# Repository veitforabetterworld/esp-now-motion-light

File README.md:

# Funklicht – vernetzter Außen-Bewegungsmelder mit 12-V-Lampe

Wemos D1 mini (ESP8266, Funk per ESP-NOW) + HC-SR501 + MOSFET auf einer **einseitigen THT-Platine (28,5 × 57 mm, v1.2)**,
in einem 3D-gedruckten, **spritzwassergeschützten Gehäuse**. Pro Board: 1 Bewegungsmelder, 1 Lampe, 1 Taster.

## Ordner

| Pfad | Inhalt |
|---|---|
| `hardware/Funklicht.kicad_pro` | KiCad-10-Projekt (Schaltplan + Platine), ERC/DRC fehlerfrei |
| `hardware/jlcpcb/Funklicht_JLCPCB_Gerber.zip` | **Fertig zum Hochladen bei JLCPCB** |
| `hardware/jlcpcb/Stueckliste.csv` | Stückliste |
| `hardware/Funklicht_Schaltplan.pdf`, `Funklicht_3D_*.png`, `Funklicht_Platine.step` | Schaltplan, Ansichten, 3D-Modell |
| `hardware/lib/` | Projekt-Footprints (D1 mini auf Buchsenleisten, Lötaugen PIR, M3-Loch). PIR-Maße nach dem 3D-Modell von [ccadic/HC-SR501](https://github.com/ccadic/HC-SR501) |
| `hardware/scripts/` | Python-Skripte, die Schaltplan und Platine erzeugen (mit KiCads `python.exe` ausführen) |
| `firmware/Funklicht/` | Firmware (ESP-NOW), Einstellungen und Lampentabelle in `config.h` |
| `gehaeuse/Funklicht_Gehaeuse.scad` | Parametrisches Gehäuse (OpenSCAD) |
| `gehaeuse/stl/` | Druckdateien |

## Schaltung

```
12V ─┬──────────────────────────────── Lampe +        Lampe − ── Drain IRLB8721 ── Source ── GND
     ├── HC-SR501 VCC (12 V)                                       Gate ── 220 Ω ── D1 (GPIO5)
     └── 1N4007 ── L7805 ── 5V D1 mini                                     └ 10 kΩ ── GND
```

| D1 mini | Funktion |
|---|---|
| D1 (GPIO5) | MOSFET → Lampe (10 kΩ Pull-down: Lampe bleibt beim Booten aus) |
| D6 (GPIO12) | PIR-Ausgang (3,3 V) |
| D5 (GPIO14) | Taster nach GND (`INPUT_PULLUP`) |
| D4 (GPIO2) | blaue Onboard-LED (Status) |

- **Klemmen** an der Stirnseite: J1 = `+12V | GND` (Einspeisung), J2 = `+ | −` (Lampe).
- **PIR**: 3 Lötaugen `V O G` (VCC, OUT, GND) – Kabel direkt anlöten. Der PIR bekommt 12 V vor der
  Verpolschutzdiode; der HC-SR501 hat selbst eine Schutzdiode, trotzdem **Polarität beim Anschließen prüfen**.
- **Lampenstrom** bis ca. 3 A (Leiterbahnen 1,5 mm, Versorgung 0,8 mm, Signale 0,5 mm; MOSFET ohne Kühlkörper). Keine Freilaufdiode: nur für
  LED-/Halogenlampen gedacht, nicht für Motoren/Relais.

## Stückliste (pro Board)

| Anz. | Teil | Hinweis |
|---|---|---|
| 1 | Wemos D1 mini (ESP8266) | auf **2 × 8-polige Buchsenleisten 8,5 mm** stecken |
| 1 | HC-SR501 | Jumper auf **H** (wiederauslösend), Zeit-Poti auf Minimum |
| 1 | L7805 (TO-220) | stehend |
| 1 | IRLB8721PBF (TO-220) | Logic-Level-MOSFET, stehend. Alternative: IRLB4132PBF (gleiche Pinbelegung und Bauhöhe). Kein Standard-MOSFET wie STP16NF06 oder IRF1404: die schalten mit 3,3 V am Gate nicht sicher durch |
| 1 | 1N4007 | Verpolschutz |
| 1 | Widerstand 220 Ω, 1/4 W | R1 |
| 1 | Widerstand 10 kΩ, 1/4 W | R2 |
| 1 | 1 µF Keramik, RM 2,5 | |
| 1 | 10 µF / 16 V Elko, Ø 5 mm, **max. 6 mm hoch** (z. B. 5 × 5) | sitzt **unter** dem D1 mini |
| 2 | Schraubklemme 2-polig, RM 5,08 | |
| 1 | Taster 6 × 6 × 5 mm, 4 Pins | Höhe 5 mm (Tastenstift ist darauf abgestimmt) |
| 11 | Einschmelzmutter M3 (z. B. M3 × 5,7, Bohrung 4,0 mm) | 4 Bodendeckel, 4 Klemmendeckel, 3 Platine |
| 4 | Senkkopfschraube M3 × 10 (DIN 7991) | Bodendeckel, bündig |
| 4 | Senkkopfschraube M3 × 8 (DIN 7991) | Klemmendeckel, bündig |
| 3 | Zylinderschraube M3 × 6 | Platine |
| 2 | Schneidschraube M2 × 6 (für Kunststoff) | PIR an die Front |
| 2 | Kabelverschraubung M12 × 1,5 | Kabel 3–6,5 mm |
| 2 | Schraube + Dübel, ca. 4 mm | Wandmontage durch die Langlöcher |

## Platine bestellen (JLCPCB)

`hardware/jlcpcb/Funklicht_JLCPCB_Gerber.zip` hochladen. Einstellungen: **2 Lagen** (gleicher Preis wie 1 Lage,
durchkontaktierte Lötaugen lassen sich besser löten – Leiterbahnen liegen trotzdem nur unten), FR-4, 1,6 mm,
HASL. Kein Bestückungsservice nötig.

**Bestückungsdruck nur auf der Unterseite** (Lötseite), die Oberseite bleibt ohne Druck. Jedes Bauteil ist dort
mit Umriss, Symbol und Wert an seiner echten Position eingezeichnet. Die Platine lässt sich allein danach bestücken:
- Widerstände mit Wert (10 kΩ, 220 Ω), Diode 1N4007 mit Ring zur Kathode
- Elko 10 µF mit `+` am eckigen Pad, 1 µF-Kondensator
- L7805 und IRLB8721: Doppellinie = Kühlfahne (Metallseite)
- D1-mini-Buchsenleisten mit Pin-1-Pfeil (RST) und „Antenne hier“
- Taster, PIR-Lötaugen `V O G`, Klemmen `+12V GND` und Lampe `+ −`

Von unten gesehen ist alles spiegelbildlich zur Oberseite. Die Bauteile also von oben einstecken und an der Markierung
auf der Unterseite ausrichten.

**Bestücken** (flach nach hoch): R1, R2, D1, C1, C2 (unter dem D1 mini!), Taster, Buchsenleisten,
Klemmen, L7805, IRLB8721. PIR-Kabel (ca. 10 cm) an `V O G` löten. Danach D1 mini aufstecken.
Unter dem D1 mini nur Bauteile bis 6 mm Höhe. Die Lötaugen `V O G` liegen in der Aussparung des D1 mini.
**Zwei Befestigungsschrauben liegen unter dem D1 mini** – Platine erst festschrauben, dann den D1 mini aufstecken.

Befestigungslöcher (Platinenkoordinaten, Ursprung oben links): H1 (4,07 / 41,39), H2 (24,0 / 32,0), H3 (7,88 / 11,54).
Der Schaltplan (`Funklicht_Schaltplan.pdf`) ist durchgehend verdrahtet: Versorgung links, D1 mini in der Mitte,
Lampenschaltung rechts, +12V-Schiene oben, GND-Schiene unten.

## Gehäuse (v2.0)

Außen ca. 42 × 81,5 × 43 mm (ohne Wandlaschen). **Öffnung nach hinten zur Wand:**

- **Gehäuse** (Haube): Seitenwände und Front aus einem Stück. In der Front sitzen das PIR-Fenster und der Taster.
  Hinten ist das Gehäuse über den vollen Innenquerschnitt (34 × 73,5 mm) offen. Die Platine passt in Einbaulage gerade
  hindurch (geprüft, auch mit L7805/MOSFET).
- **Bodendeckel** (Wandseite): trägt die Platine auf drei Domen (Ø 6,5 mm, berühren keine Lötstelle) und die beiden
  Wandlaschen. Die Laschen haben gerundete Ecken und je ein Langloch (Ø 4,8 mm, 3 mm Verschiebeweg), um 45° gedreht und
  oben/unten spiegelbildlich (`/` und `\`). Zusammen gleichen die beiden Langlöcher ungenau gebohrte Wandlöcher in jeder Richtung aus.
  Der Bodendeckel wird mit 4 M3-Senkkopfschrauben von hinten bündig an das Gehäuse geschraubt. Die Schrauben greifen in
  Einschmelzmuttern in den vier Eckblöcken am hinteren Rand. Die Eckblöcke liegen außerhalb des Platinenumrisses.
- **Dichtung**: TPU-Schnur in einer Nut im hinteren Gehäuserand, innerhalb der Schrauben, rundum geschlossen.
  Die Dichtfläche liegt an der geschützten Wandseite, nicht mehr an der Front. Ein Zentrierkragen am Bodendeckel führt
  ihn ins Gehäuse.
- **PIR** (HC-SR501, Platine 32 × 24 mm): sitzt mittig auf der Front hinter dem Klemmendeckel. Er wird mit seinen
  **2 Befestigungslöchern** (Ø 2 mm, Abstand 28 mm, am Bauteil gemessen) von innen an zwei kurze Dome in der Front
  geschraubt (M2 × 6, Kunststoff-Schneidschraube / Blechschraube 2,2 mm). Die Löcher in den Domen (Ø 1,7 mm) sind
  Sacklöcher und von außen nicht sichtbar. Die Linsendichtung liegt zwischen Linsenplatte und Front.
- **Taster** bei geschlossenem Gehäuse: nur zwei Teile, die Front mit Führungsrohr und ein Tastenstift.
  - Das Loch in der Front ist als **Rohr** (außen Ø 7,6 mm, Bohrung Ø 4,4 mm) bis 1 mm über den Stiftkopf nach innen
    verlängert, rund 21 mm lange Führung.
  - Der **Tastenstift** (Ø 4 mm) hat unten einen Kopf (Ø 6,5 mm), der auf dem Taster aufliegt. Er steht in Ruhe 1 mm aus
    der Front; der Ring auf der Front markiert die Stelle. Der Kopf verhindert, dass der Stift nach außen herausfällt.
  - Die Stiftdurchführung ist **nicht gedichtet** (0,2 mm Spiel rundum). Bei senkrechter Front und waagrechtem Rohr
    kommt kaum Wasser hinein, ganz dicht wie die Deckel ist sie aber nicht.
- **Kabelverschraubungen** (2 × M12 × 1,5) in der unteren Stirnseite, 16 mm über der Dichtfläche und damit nahe an den
  Klemmeneingängen. Zwischen den Kontermuttern innen und den Klemmen bleiben knapp 4 mm, kein Leerraum mehr. Die
  Kontermuttern (SW 15) mit einer Schlüsselfläche zur Seitenwand drehen; so sind sie frei (geprüft, `kollision_kontermutter`).
- **Klemmendeckel** vorne über den Schraubklemmen: kleiner Schraubdeckel mit 4 M3-Senkkopfschrauben (bündig) und
  eigener TPU-Dichtung. Ein **Quersteg** direkt hinter den Klemmen trennt den Klemmenraum vorne ab und trägt die Dichtung.
  Bei abgenommenem Deckel kommt ein Schraubendreher (Ø 3 mm) senkrecht an alle vier Klemmenschrauben (geprüft).
  Kabel lassen sich so anschließen, ohne das Gehäuse von der Wand zu nehmen. Weil auch dieser Deckel gedichtet ist,
  ist der ganze Innenraum dicht.

Kollisionsprüfungen in der SCAD-Datei (`part` = `kollision`, `kollision_taster`, `kollision_bodendeckel`,
`kollision_klemmdeckel`, `kollision_schraubendreher`, `kollision_kontermutter`, `kollision_einbau`) liefern nur Flächenkontakte bzw. ein leeres
Objekt. `kollision_einbau` prüft, dass die bestückte Platine von hinten bis in ihre Endlage geschoben werden kann.

| Teil (`gehaeuse/stl/`) | Material | Druck |
|---|---|---|
| `gehaeuse.stl` | PETG | Front aufs Bett (schon gedreht), ohne Stützen (Eckblöcke mit 45°-Fase) |
| `bodendeckel.stl` | PETG | Wandseite aufs Bett |
| `klemmdeckel.stl` | PETG | Außenseite aufs Bett (schon gedreht) |
| `tastenstift.stl` | PETG | Kopf aufs Bett |
| `regenschutz.stl` (optional) | PETG | flach, über die Linse kleben |
| `dichtung.stl` | TPU 95A | flach, 100 % Infill (Bodendeckel) |
| `klemmdichtung.stl` | TPU 95A | flach, 100 % Infill (Klemmendeckel, gleiche Schnur 1,8 mm) |
| `linsendichtung.stl` | TPU 95A | flach |

**Montage**:
1. Einschmelzmuttern M3 mit dem Lötkolben setzen: 4 im hinteren Gehäuserand, 4 für den Klemmendeckel,
   3 in den Platinendomen des Bodendeckels.
2. Von hinten ins Gehäuse: PIR mit Linsendichtung auf die Dome schrauben. Gehäuse mit der Front nach unten legen und
   den Tastenstift (Spitze voran) ins Rohr stecken.
3. Platine auf den Bodendeckel schrauben, dann den D1 mini aufstecken.
4. Dichtung in die hintere Nut legen, Bodendeckel einsetzen und mit 4 M3 × 10 Senkkopfschrauben von hinten verschrauben.
5. Das Gehäuse **mit den Kabelverschraubungen nach unten** über die Laschen des Bodendeckels an die Wand schrauben.
6. Kabel durch die Verschraubungen führen und durch die vordere Öffnung anklemmen. Klemmdichtung in die Nut legen und
   den Klemmendeckel mit 4 M3 × 8 Senkkopfschrauben aufschrauben.

## Firmware (ESP-NOW)

`firmware/Funklicht/Funklicht.ino` ist eine Firmware für alle Lampen. Board: **LOLIN(WEMOS) D1 R2 & mini**.
Benötigte Bibliothek: **QuickEspNow 0.8.1** (German Martín, MIT), über den Bibliotheksverwalter der Arduino-IDE installieren.

**Schlüssel anlegen:** Die Firmware erwartet eine Arduino-Bibliothek `Secrets` mit dem gemeinsamen Schlüssel.
Sie ist absichtlich nicht im Repository. Anlegen unter `<Sketchbook>/libraries/Secrets/`:

```
libraries/Secrets/library.properties   name=Secrets
                                        version=1.0.0
libraries/Secrets/src/Secrets.h        #pragma once
                                        #define FUNKLICHT_KEY "eigener-langer-zufaelliger-schluessel"
```

Alle Lampen einer Anlage brauchen denselben Schlüssel.

**Funk mit Empfangsbestätigung**:
- Nachrichten gehen gezielt (Unicast) an die gekoppelten Lampen.
- Der Empfänger bestätigt jede Nachricht, und QuickEspNow wartet im synchronen Modus auf diese Bestätigung.
- Fehlt sie, sendet die Firmware bis zu 4-mal erneut, ähnlich wie TCP. Danach meldet sie im seriellen Monitor `Keine Bestaetigung von …`.
- Gesendet werden nur Zustandswechsel, keine Wiederholungen: je Lampe und Durchgang eine Meldung „Bewegung beginnt“ und eine Meldung „Ruhe“ bzw. „Person weiter“ an jeden Partner.
  Nur bei mehr als 2 Minuten ununterbrochener Bewegung wird die Meldung einmal aufgefrischt.
  Fällt eine Lampe aus, bevor sie „Ruhe“ melden kann, gehen ihre Nachbarn nach spätestens 5 Minuten aus.
- Alle 5 Minuten prüft jede Lampe, ob ihre Partner noch antworten.
- Protokollversion 3: Alle Lampen müssen dieselbe Firmware haben.

**Pairing (Lampen koppeln)**, dynamisch über die feste MAC-Adresse, ohne Neu-Kompilieren:

1. An Lampe A den Taster **1 s halten**. As Lampe blinkt schnell, und A sucht 30 s lang einen Partner.
   Alle Lampen, die schon mit A gekoppelt sind, **blinken langsam** mit. So sieht man sofort, welche gekoppelt sind.
2. An einer **nicht blinkenden** Lampe B den Taster 1 s halten: A und B finden sich automatisch und speichern sich
   gegenseitig im Flash. Zur Bestätigung leuchten beide Lampen 1,5 s lang, danach ist der Pairing-Modus beendet.
3. An einer **langsam blinkenden** Lampe den Taster 1 s halten: Die Kopplung zu A wird auf beiden Seiten gelöst.
   Beide leuchten 1,5 s zur Bestätigung. A bleibt im Pairing-Modus (wieder 30 s), so lassen sich mehrere Lampen nacheinander entkoppeln.

Die blaue LED auf dem D1 mini zeigt dasselbe Muster wie die Lampe.

Jede Lampe kann bis zu 8 Partner haben. Gekoppelt werden **benachbarte** Lampen, also die, die bei Bewegung mit vorleuchten sollen (z. B. Garage links ↔ Garage Mitte ↔ Garage rechts ↔ Haustür).
Koppeln können sich nur Lampen mit demselben Schlüssel
(`FUNKLICHT_KEY` in `libraries/Secrets/src/Secrets.h`, alle Nachrichten sind mit HMAC-SHA256 signiert).

**Verhalten**:

| Ereignis | Reaktion |
|---|---|
| Bewegung am eigenen PIR | Licht an bis 60 s nach der letzten Bewegung. Die gekoppelten Lampen bekommen **eine** Meldung „Bewegung beginnt“ |
| 30 s keine Bewegung mehr | Meldung „Ruhe“ an die gekoppelten Lampen, diese gehen aus |
| Gekoppelte Lampe meldet Bewegung | Licht leuchtet vor, bis diese Lampe „Ruhe“ oder „Person weiter“ meldet |
| Person geht von Lampe A zu Lampe B weiter | A meldet „Person weiter“. A und die von A vorgeleuchteten Lampen gehen nach 8 s aus, das Licht folgt der Person. Sieht As PIR die Person noch, erst wenn er abfällt. Weitere Meldungen von B lassen A nicht wieder vorleuchten |
| Taster kurz | wie Bewegung am PIR: Licht an, gekoppelte Lampen werden informiert |
| Taster lang (ab 1 s) | Pairing-Modus. Blinkt die Lampe gerade langsam (Partner ist im Pairing-Modus): Kopplung lösen |

Weitere Eigenschaften:
- Die Lampe wird weich per PWM ein- und ausgeblendet. Flackert ein LED-Treiber, `DIMMEN = false` setzen.
- Der PIR wird 60 s lang ignoriert, solange er anläuft; in dieser Zeit blinkt die LED langsam.
- Ein PIR-Signal zählt erst, wenn es 100 ms ansteht.
- Die Sendeleistung ist auf 17 dBm reduziert.

Alle Einstellungen stehen in `config.h`. Den seriellen Monitor mit 115200 Baud öffnen: Dort zeigt jede Lampe ihre MAC, ihre Partner und alle Funkereignisse.
## Hinweise / offen

- **Fehlauslöser durch Funk:** Der PIR sitzt nah am ESP8266. Gegenmaßnahmen:
  - Der PIR wird mit 12 V versorgt und ist so von der 5-V-Versorgung des ESP getrennt.
  - Der PIR sitzt über dem USB-Ende des Moduls, von der Antenne weg.
  - In der Firmware lässt sich die Sendeleistung reduzieren (`WiFi.setOutputPower()`), eine Entprellung von ca. 100 ms einbauen und die ersten 60 s nach dem Start ignorieren.
- **Ungeprüfte Annahmen:**
  - Die PIR-Maße stammen aus dem 3D-Modell und sind nicht nachgemessen.
  - Die Bauteilhöhen sind Schätzwerte.
  - Vor dem ersten Druck einmal PIR-Platine, Linsendurchmesser (Lochabstand 28 mm ist gemessen) nachmessen. Die Werte stehen oben in der `.scad` (`pir_hole_dx`).
- **Firmware:** kompiliert fehlerfrei, ist aber noch nicht auf echter Hardware mit mehreren Lampen getestet.

## Lizenz

[PolyForm Noncommercial 1.0.0](LICENSE): frei nutzbar, veränderbar und weitergebbar, aber nur nicht kommerziell. Keine Gewährleistung, keine Haftung.

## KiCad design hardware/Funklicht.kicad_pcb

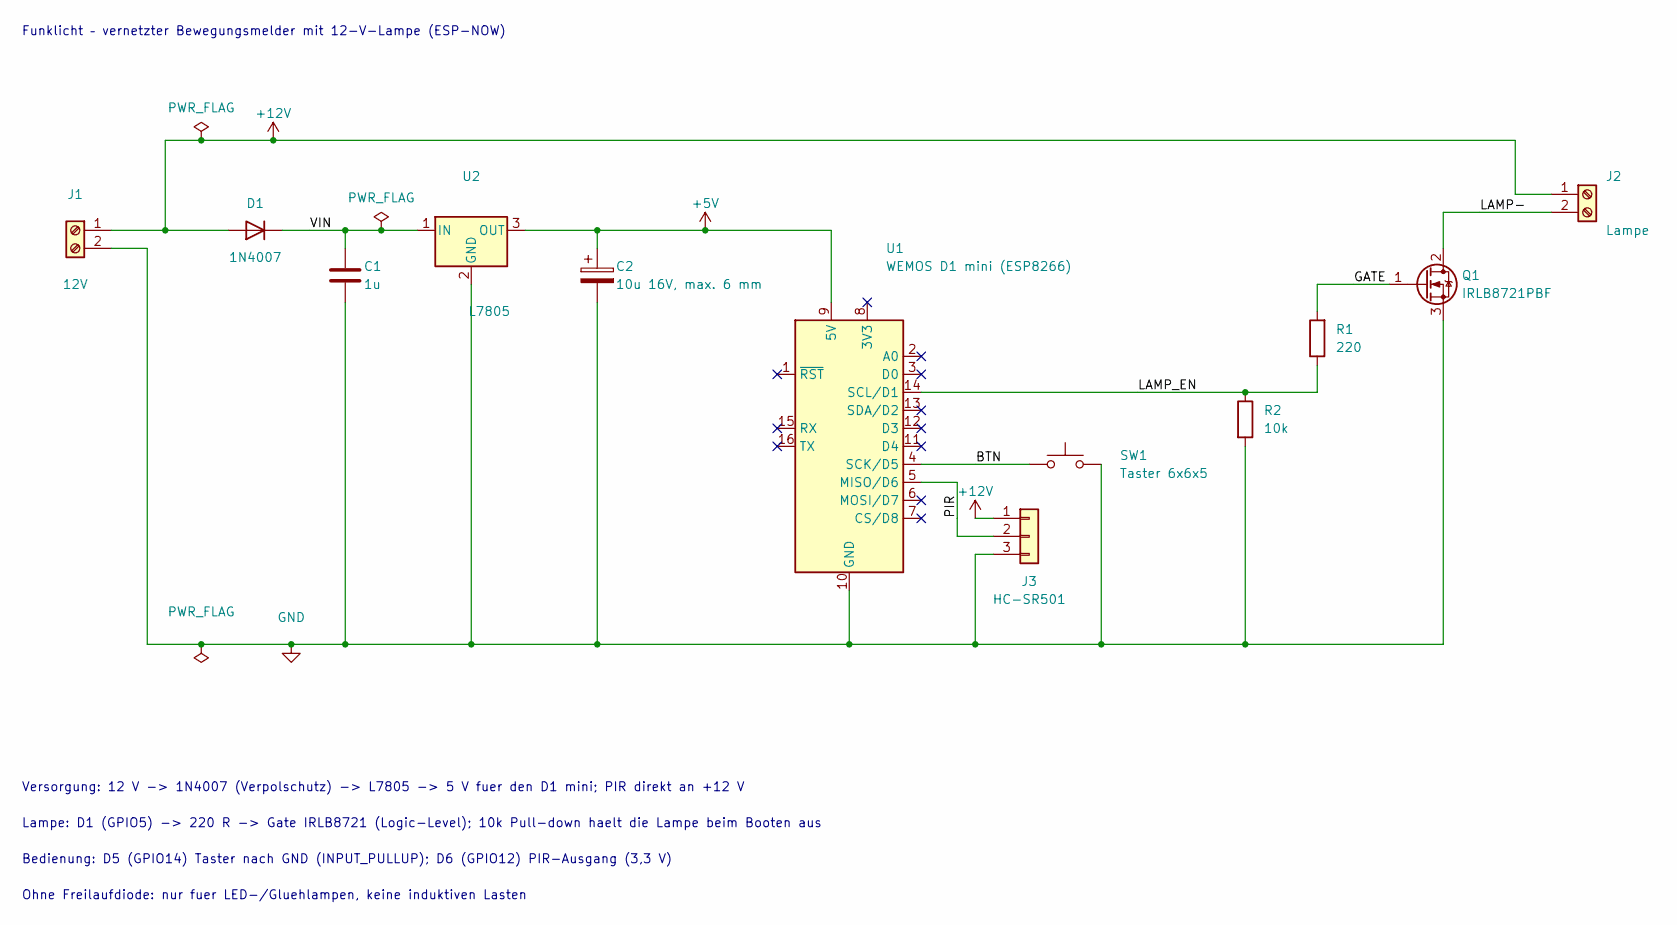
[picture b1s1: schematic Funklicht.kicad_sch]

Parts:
C1: 1u; C_Disc_D3.0mm_W1.6mm_P2.50mm
C2: 10u 16V, max. 6 mm; CP_Radial_D5.0mm_P2.50mm
D1: 1N4007; D_DO-41_SOD81_P10.16mm_Horizontal
J1: 12V; TerminalBlock_Phoenix_MKDS-1,5-2-5.08_1x02_P5.08mm_Horizont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
J2: Lampe; TerminalBlock_Phoenix_MKDS-1,5-2-5.08_1x02_P5.08mm_Horizont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
J3: HC-SR501; Loetaugen_1x03_P2.54mm
Q1: IRLB8721PBF; TO-220-3_Vertical
R1: 220; R_Axial_DIN0207_L6.3mm_D2.5mm_P10.16mm_Horizontal
R2: 10k; R_Axial_DIN0207_L6.3mm_D2.5mm_P10.16mm_Horizontal
SW1: Taster 6x6x5; SW_PUSH_6mm
U1: WEMOS D1 mini (ESP8266); WEMOS_D1_mini_Sockel
U2: L7805; TO-220-3_Vertical

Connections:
+5V: C2.1, U1.9 (5V), U2.3 (OUT)
+12V: D1.2 (A), J1.1, J2.1, J3.1
/BTN: SW1.1, U1.4 (SCK/D5)
/GATE: Q1.1 (G), R1.2
/LAMP-: J2.2, Q1.2 (D)
/LAMP_EN: R1.1, R2.1, U1.14 (SCL/D1)
/PIR: J3.2, U1.5 (MISO/D6)
/VIN: C1.1, D1.1 (K), U2.1 (IN)
GND: C1.2, C2.2, J1.2, J3.3, Q1.3 (S), R2.2, SW1.2, U1.10 (GND), U2.2 (GND)

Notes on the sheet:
Funklicht – vernetzter Bewegungsmelder mit 12-V-Lampe (ESP-NOW)
Versorgung: 12 V -> 1N4007 (Verpolschutz) -> L7805 -> 5 V fuer den D1 mini; PIR direkt an +12 V
Lampe: D1 (GPIO5) -> 220 R -> Gate IRLB8721 (Logic-Level); 10k Pull-down haelt die Lampe beim Booten aus
Bedienung: D5 (GPIO14) Taster nach GND (INPUT_PULLUP); D6 (GPIO12) PIR-Ausgang (3,3 V)
Ohne Freilaufdiode: nur fuer LED-/Gluehlampen, keine induktiven Lasten

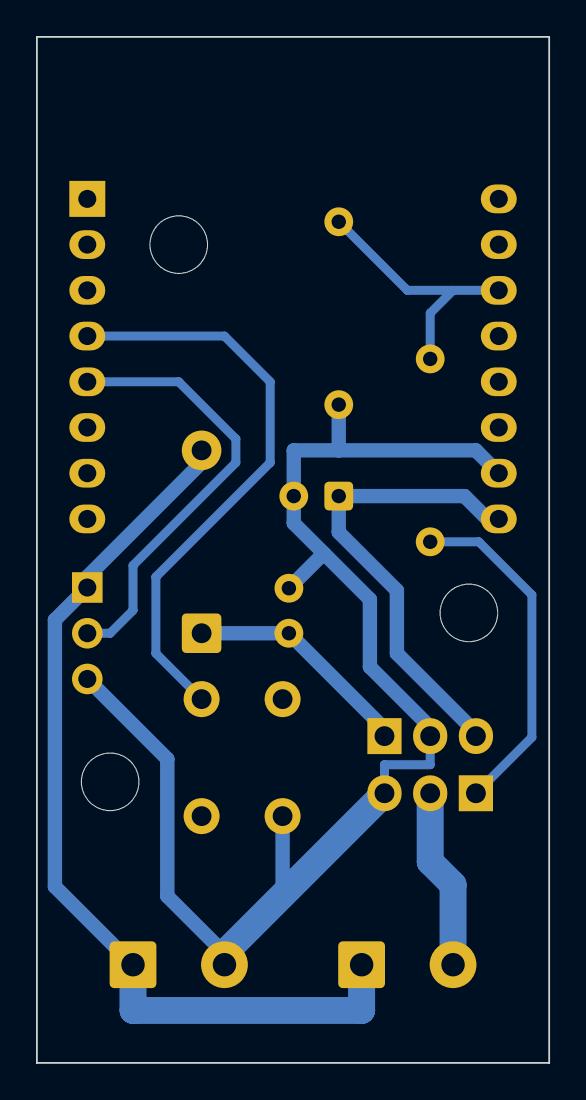
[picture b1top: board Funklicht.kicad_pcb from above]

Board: 2 copper layers, 28.5 x 57.0 mm, 15 parts (0 on the bottom side), 9 nets.

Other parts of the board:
H1, H2, H3: M3; MountingHole_3.2mm_M3_Kopf5.5

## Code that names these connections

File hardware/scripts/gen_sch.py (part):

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power('GND', (68.58, YG))
for p in ((55.88, Y12), (81.28, 58.42), (55.88, YG)):   # PWR_FLAG: +12V, VIN, GND
    power('PWR_FLAG', p, 0 if p[1] != YG else 180)
LABELS = [('VIN', (71.12, 58.42), 0), ('LAMP_EN', (187.96, 81.28), 0), ('GATE', (218.44, 66.04), 0),
          ('LAMP-', (236.22, 55.88), 0), ('BTN', (165.10, 91.44), 0), ('PIR', (162.56, 99.06), 90)]
for name, (x, y), ang in LABELS:
    out.append(['label', q(name), ['at', fmt(x), fmt(y), str(ang)], font(justify='left bottom'), ['uuid', q(U())]])
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texts = [
    ("Funklicht – vernetzter Bewegungsmelder mit 12-V-Lampe (ESP-NOW)", 30.48, 30.48),
    ("Versorgung: 12 V -> 1N4007 (Verpolschutz) -> L7805 -> 5 V fuer den D1 mini; PIR direkt an +12 V", 30.48, 137.16),
    ("Lampe: D1 (GPIO5) -> 220 R -> Gate IRLB8721 (Logic-Level); 10k Pull-down haelt die Lampe beim Booten aus", 30.48, 142.24),
    ("Bedienung: D5 (GPIO14) Taster nach GND (INPUT_PULLUP); D6 (GPIO12) PIR-Ausgang (3,3 V)", 30.48, 147.32),
    ("Ohne Freilaufdiode: nur fuer LED-/Gluehlampen, keine induktiven Lasten", 30.48, 152.40),
]
for t, x, y in texts:
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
